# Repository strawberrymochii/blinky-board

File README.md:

# blinky-board
This is a blinky board design I made using KiCad as my first hardware project. This board uses a 555 timer to flash LEDs. While working on this blinky board, I followed a tutorial, and I learned how to use the KiCad software. Figuring out where all the parts of the board went was very difficult at first, but I was able to get a hang of it in the end. The hardest part for me was importing a new footprint library, since a there were a lot of new terms to navigate. Overall, this project was super informative in learning the basics of PCB design.

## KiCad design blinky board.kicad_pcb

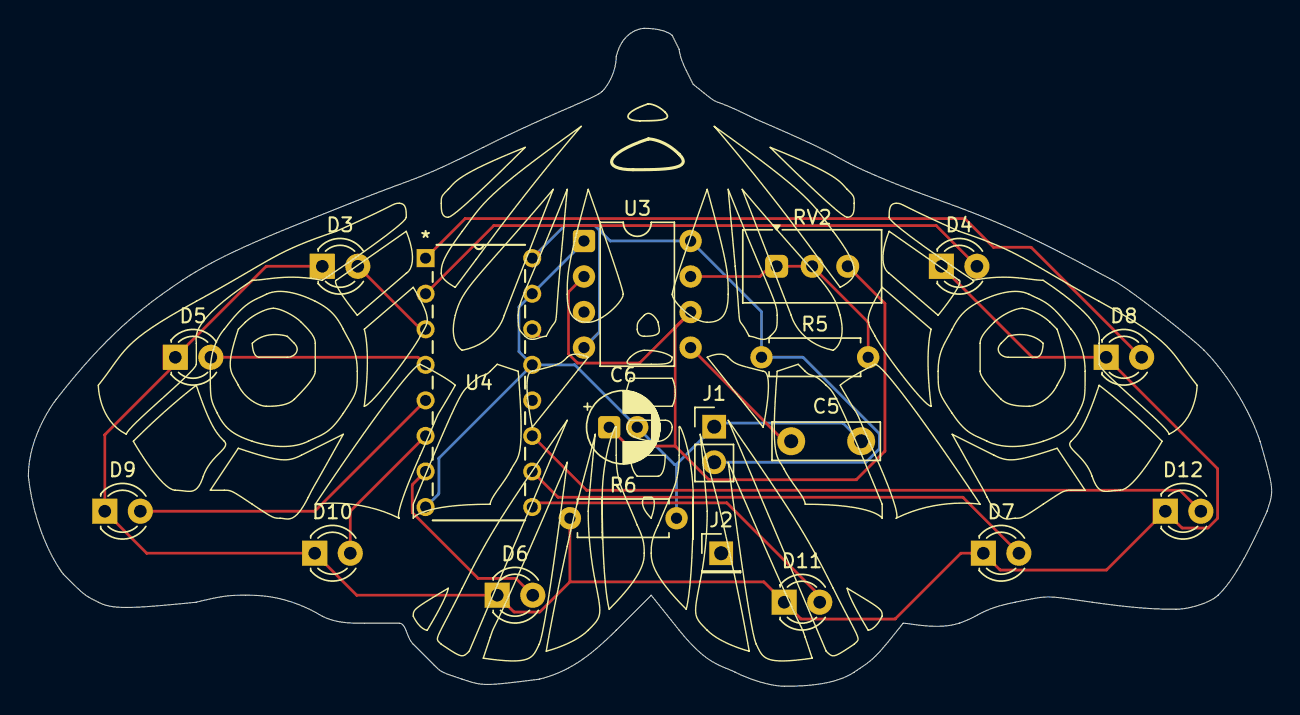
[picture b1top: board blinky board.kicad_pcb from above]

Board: 2 copper layers, 88.8 x 47.0 mm, 19 parts (0 on the bottom side), 16 nets.

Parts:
C5: 0.01 uF; C_Disc_D7.5mm_W2.5mm_P5.00mm
C6: 1 uF; CP_Radial_D5.0mm_P2.00mm
D3, D4, D5, D6, D7, D8, D9, D10, D11, D12: LED; LED_D3.0mm
J1: Conn_01x02_Socket; PinHeader_1x02_P2.54mm_Vertical
J2: Conn_01x01_Socket; PinHeader_1x01_P2.54mm_Vertical
R5: 1k; R_Axial_DIN0207_L6.3mm_D2.5mm_P7.62mm_Horizontal
R6: 470; R_Axial_DIN0207_L6.3mm_D2.5mm_P7.62mm_Horizontal
RV2: 50k; Potentiometer_Vishay_T93YA_Vertical
U3: NE555P; DIP-8_W7.62mm
U4: 4017; N16

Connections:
+5V: J1.2, R5.1, U3.4 (~RST), U3.8 (VCC), U4.16 (VDD)
GND: C5.2, C6.2, J1.1, R6.2, U3.1 (GND), U4.8 (VSS), U4.13 (CKEN), U4.15 (Reset)
unnamed: D3.2 (A), U4.3 (Q0)
unnamed: D4.2 (A), U4.2 (Q1)
unnamed: D5.2 (A), U4.4 (Q2)
unnamed: D6.2 (A), U4.7 (Q3)
unnamed: D7.2 (A), U4.10 (Q4)
unnamed: D8.2 (A), U4.1 (Q5)
unnamed: D9.2 (A), U4.5 (Q6)
unnamed: D10.2 (A), U4.6 (Q7)
unnamed: D3.1 (K), D4.1 (K), D5.1 (K), D6.1 (K), D7.1 (K), D8.1 (K), D9.1 (K), D10.1 (K), D11.1 (K), D12.1 (K), R6.1
unnamed: D11.2 (A), U4.9 (Q8)
unnamed: D12.2 (A), U4.11 (Q9)
unnamed: C5.1, U3.5 (CONT)
unnamed: R5.2, RV2.1, RV2.2, U3.7 (DISCH)
TR: C6.1, RV2.3, U3.2 (TRIG), U3.6 (THRES)

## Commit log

2026-04-15 Enhance README with project details
2026-04-15 Enhance README with additional project details
    Expanded the project description to include details about the 555 timer and the learning process with KiCad.
2026-04-15 Enhance README with detailed project experience
    Expanded project description to include challenges faced and insights gained during the design process.
